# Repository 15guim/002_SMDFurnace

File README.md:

# 002_SMDFurnace
A furnace used to solder pieces on a PCB

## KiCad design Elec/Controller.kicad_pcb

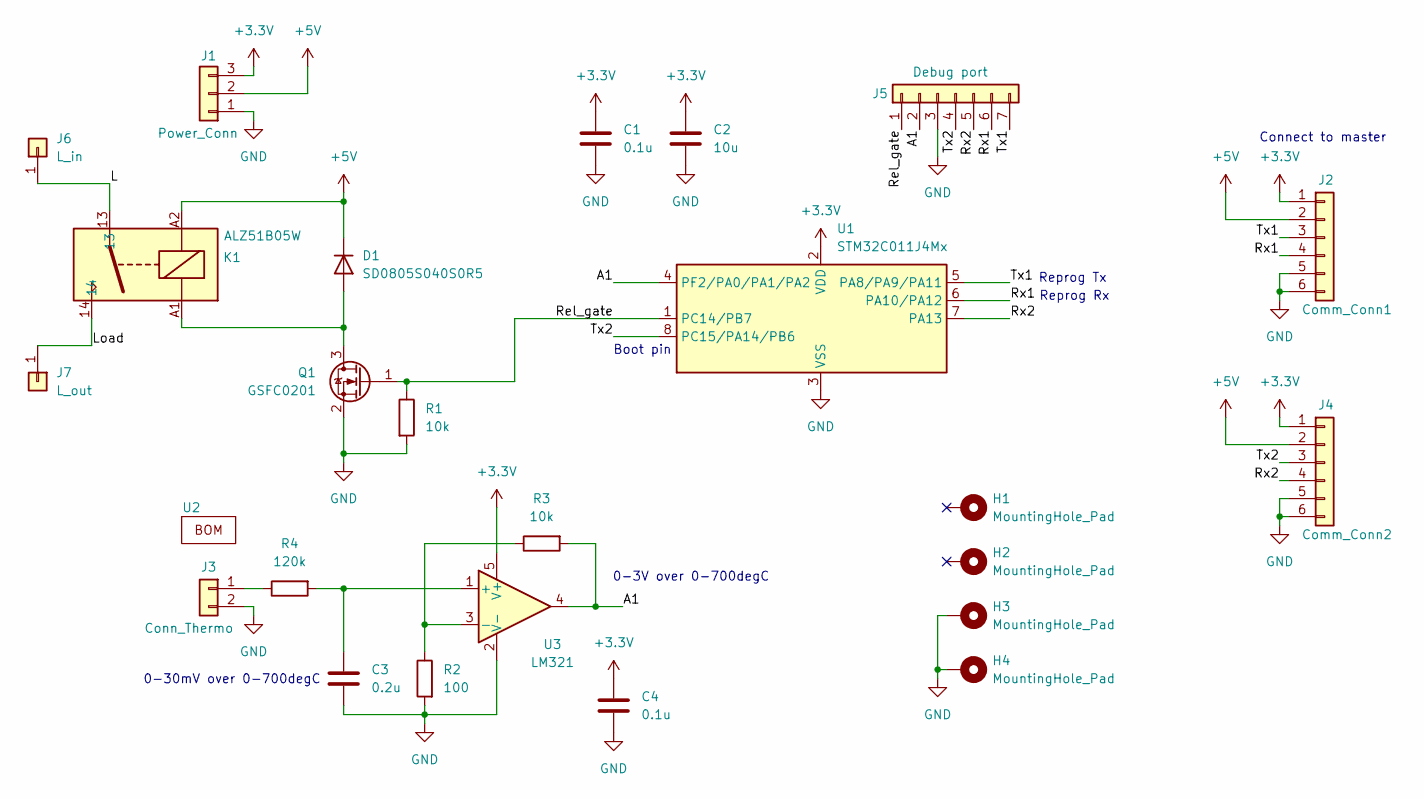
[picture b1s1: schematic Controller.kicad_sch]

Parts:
C1, C4: 0.1u; C_0603_1608Metric
C2: 10u; C_0603_1608Metric
C3: 0.2u; C_0603_1608Metric
D1: SD0805S040S0R5; D_0805_2012Metric
H1, H2, H3, H4: MountingHole_Pad; MountingHole_2.2mm_M2_DIN965_Pad_TopBottom
J1: Power_Conn; PinHeader_1x03_P2.54mm_Vertical
J2: Comm_Conn1; PHY_comm_diffV1
J3: Conn_Thermo; PinHeader_1x02_P2.54mm_Vertical
J4: Comm_Conn2; PHY_comm_diffV1
J5: Debug port; PinHeader_1x07_P2.54mm_Vertical
J6: L_in; Pad_14AWG_TopBottom_custom
J7: L_out; Pad_14AWG_TopBottom_custom
K1: ALZ51B05W
Q1: GSFC0201; SOT-23-3
R1, R3: 10k; C_0603_1608Metric
R2: 100; R_0603_1608Metric
R4: 120k; R_0603_1608Metric
U1: STM32C011J4Mx; SOIC-8_3.9x4.9mm_P1.27mm
U2: (no value)
U3: LM321; SOT-23-5

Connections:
+3.3V: C1.1, C2.1, C4.1, J1.3, J2.1, J4.1, U1.2 (VDD), U3.5 (V+)
+5V: D1.1 (K), J1.2, J2.2, J4.2, K1.A2
/A1: J5.2, R3.2, U1.4 (PF2/PA0/PA1/PA2), U3.4
/L: J6.1, K1.12 (13), K1.13
/Load: J7.1, K1.14, K1.15 (14)
/Rel_gate: J5.1, Q1.1 (G), R1.1, U1.1 (PC14/PB7)
/Rx1: J2.4, J5.6, U1.6 (PA10/PA12)
/Rx2: J4.4, J5.5, U1.7 (PA13)
/Tx1: J2.3, J5.7, U1.5 (PA8/PA9/PA11)
/Tx2: J4.3, J5.4, U1.8 (PC15/PA14/PB6)
GND: C1.2, C2.2, C3.2, C4.2, H3.1, H4.1, J1.1, J2.5, J2.6, J3.2, J4.5, J4.6, J5.3, Q1.2 (S), R1.2, R2.2, U1.3 (VSS), U3.2 (V-)
unnamed: D1.2 (A), K1.A1, Q1.3 (D)
unnamed: J3.1, R4.1
unnamed: C3.1, R4.2, U3.1 (+)
unnamed: R2.1, R3.1, U3.3 (-)

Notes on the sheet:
Boot pin
0-30mV over 0-700degC
Reprog Rx
Connect to master
0-3V over 0-700degC
Reprog Tx

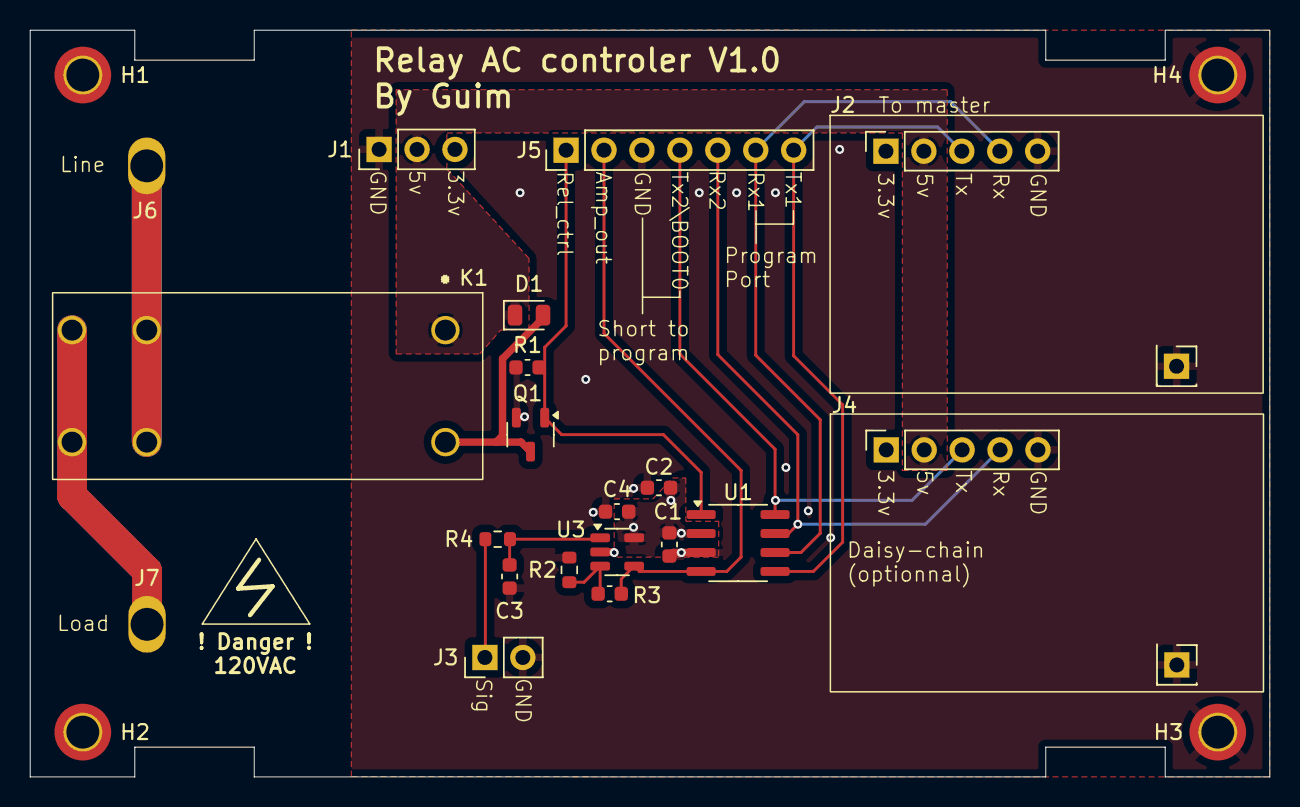
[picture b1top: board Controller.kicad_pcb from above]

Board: 4 copper layers, 83.0 x 50.0 mm, 24 parts (0 on the bottom side), 15 nets.

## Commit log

2025-02-25 Initial commit
    Getting up to speed...
